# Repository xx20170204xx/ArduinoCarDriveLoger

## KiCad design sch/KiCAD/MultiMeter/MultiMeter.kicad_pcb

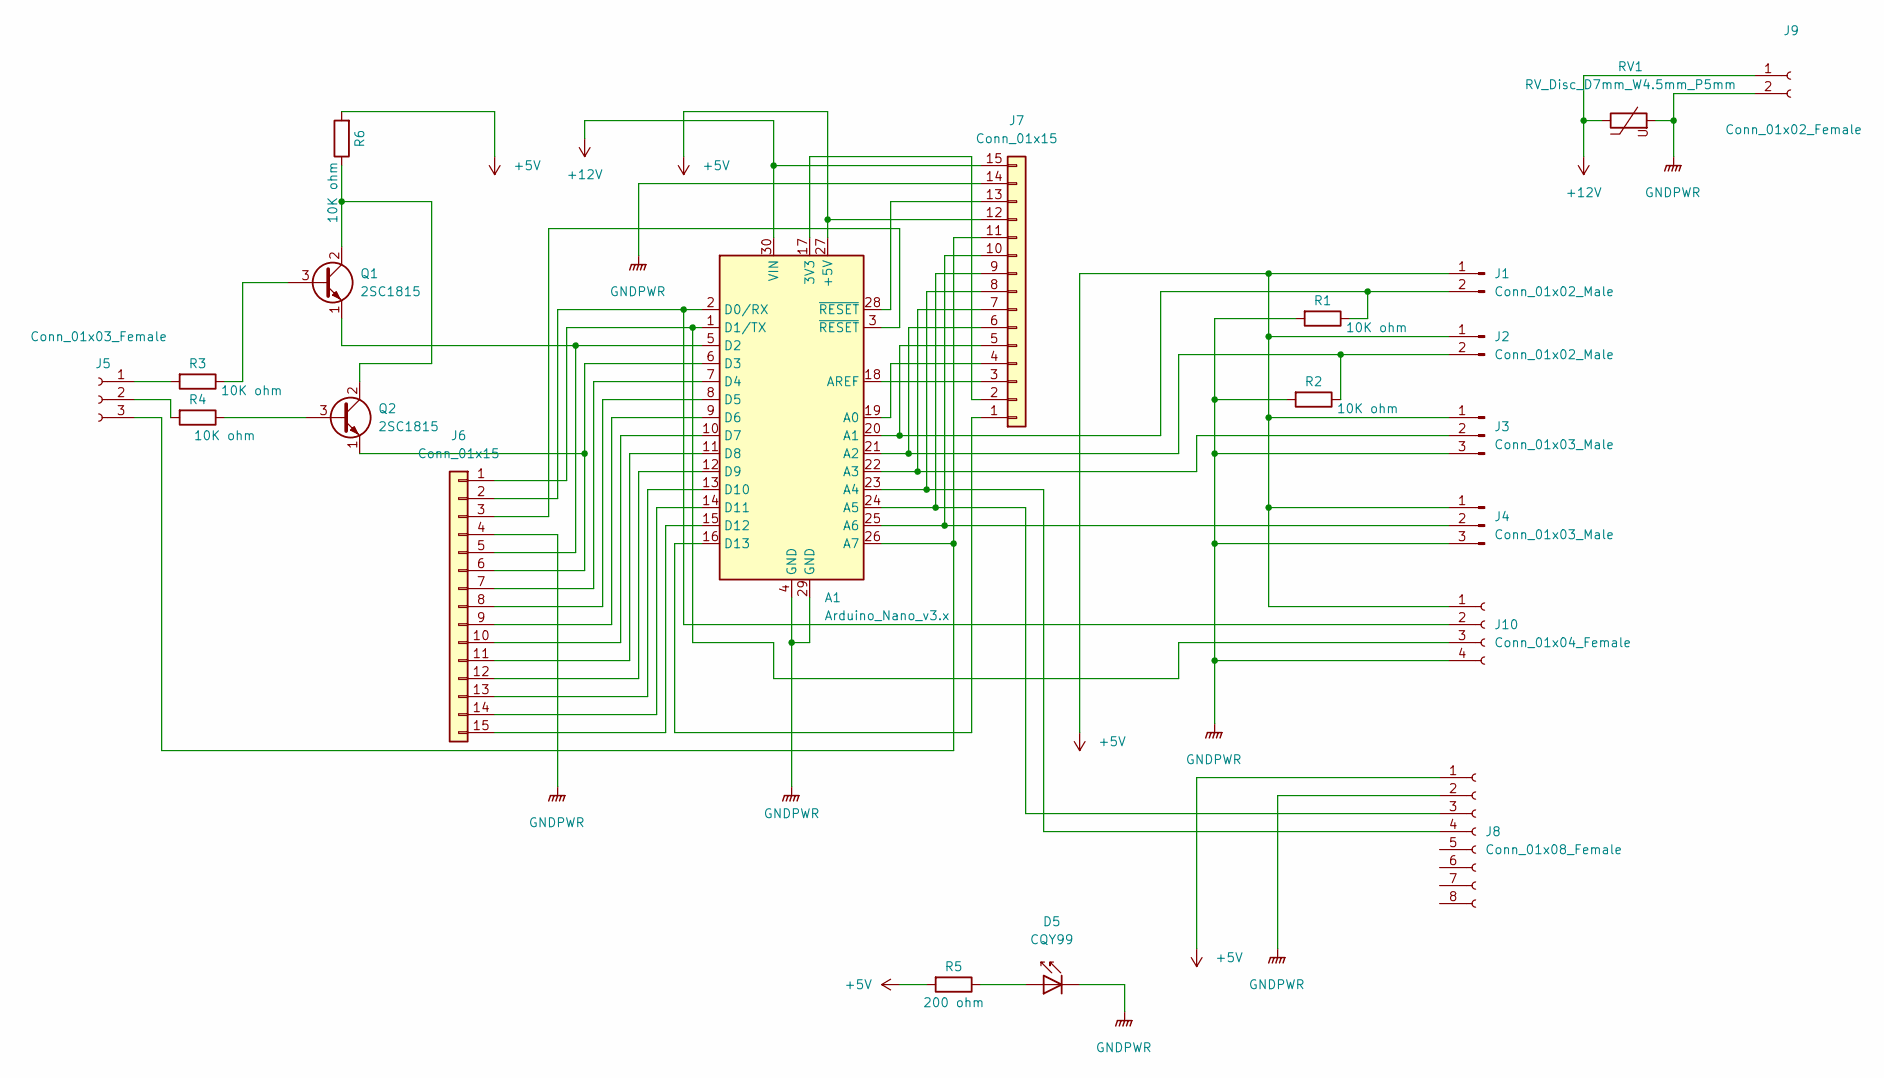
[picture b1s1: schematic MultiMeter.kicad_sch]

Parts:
A1: Arduino_Nano_v3.x; Arduino_Nano
D5: CQY99; LED_D5.0mm_IRGrey
J1, J2: Conn_01x02_Male; Molex_SPOX_5268-02A_1x02_P2.50mm_Horizontal
J3, J4: Conn_01x03_Male; Molex_SPOX_5268-03A_1x03_P2.50mm_Horizontal
J5: Conn_01x03_Female; Molex_KK-254_AE-6410-03A_1x03_P2.54mm_Vertical
J6, J7: Conn_01x15; PinSocket_1x15_P2.54mm_Vertical
J8: Conn_01x08_Female; JST_XH_S8B-XH-A-1_1x08_P2.50mm_Horizontal
J9: Conn_01x02_Female; Molex_KK-254_AE-6410-02A_1x02_P2.54mm_Vertical
J10: Conn_01x04_Female; Molex_SPOX_5268-04A_1x04_P2.50mm_Horizontal
Q1, Q2: 2SC1815; TO-92_Inline
R1, R2, R3, R4, R6: 10K ohm; R_Axial_DIN0204_L3.6mm_D1.6mm_P7.62mm_Horizontal
R5: 200 ohm; R_Axial_DIN0204_L3.6mm_D1.6mm_P7.62mm_Horizontal
RV1: RV_Disc_D7mm_W4.5mm_P5mm

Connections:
+5V: A1.27 (+5V), J1.1, J2.1, J3.1, J4.1, J7.12, J8.1, J10.1, R5.2, R6.2
+12V: A1.30 (VIN), J7.15, J9.1, RV1.1
GNDPWR: A1.4 (GND), A1.29 (GND), D5.1 (K), J3.3, J4.3, J6.4, J7.14, J8.2, J9.2, J10.4, R1.2, R2.2, RV1.2
unnamed: A1.17 (3V3), J7.2
unnamed: A1.19 (A0), J7.4
unnamed: A1.20 (A1), J1.2, J7.5, R1.1
unnamed: A1.21 (A2), J2.2, J7.6, R2.1
unnamed: A1.22 (A3), J3.2, J7.7
unnamed: A1.23 (A4), J7.8, J8.4
unnamed: A1.24 (A5), J7.9, J8.3
unnamed: A1.25 (A6), J4.2, J7.10
unnamed: A1.26 (A7), J5.3, J7.11
unnamed: A1.18 (AREF), J7.3
unnamed: A1.2 (D0/RX), J6.2, J10.2
unnamed: A1.1 (D1/TX), J6.1, J10.3
unnamed: A1.5 (D2), J6.5, Q1.1 (E)
unnamed: A1.6 (D3), J6.6, Q2.1 (E)
unnamed: A1.7 (D4), J6.7
unnamed: A1.8 (D5), J6.8
unnamed: A1.9 (D6), J6.9
unnamed: A1.10 (D7), J6.10
unnamed: A1.11 (D8), J6.11
unnamed: A1.12 (D9), J6.12
unnamed: A1.13 (D10), J6.13
unnamed: A1.14 (D11), J6.14
unnamed: A1.15 (D12), J6.15
unnamed: A1.16 (D13), J7.1
unnamed: D5.2 (A), R5.1
unnamed: J5.1, R3.2
unnamed: J5.2, R4.2
unnamed: A1.3 (~RESET), J6.3
unnamed: A1.28 (~RESET), J7.13
unnamed: Q1.3 (B), R3.1
unnamed: Q1.2 (C), Q2.2 (C), R6.1
unnamed: Q2.3 (B), R4.1

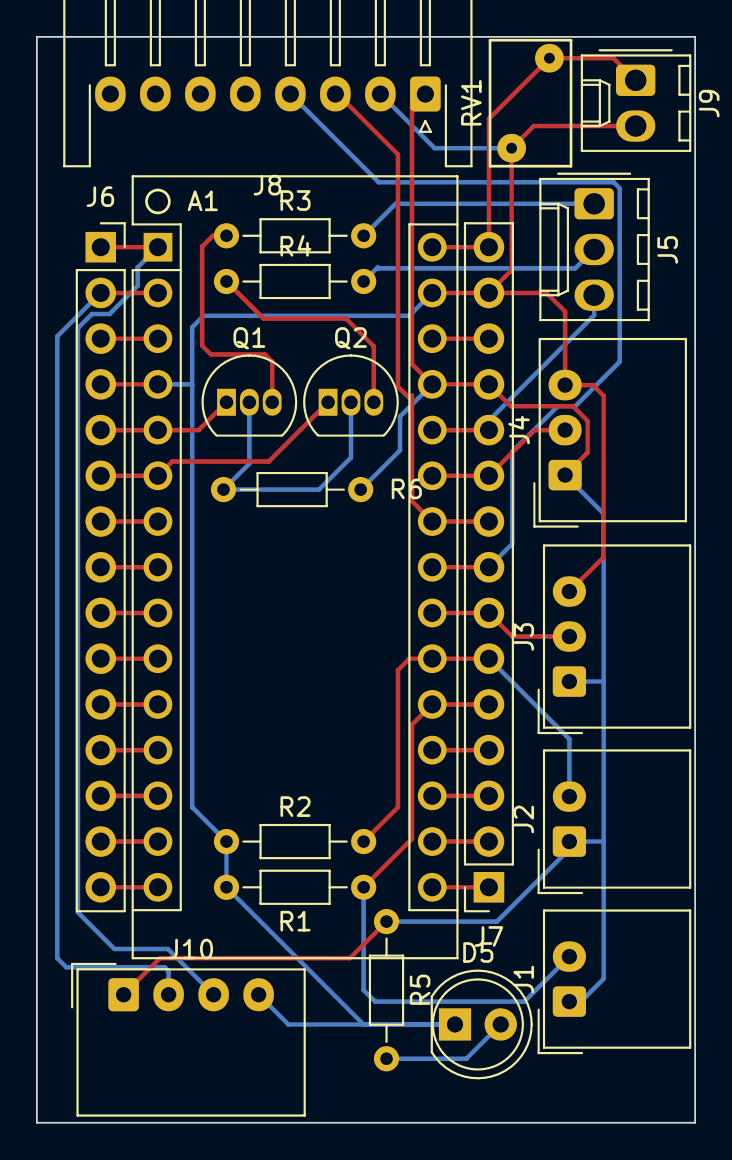
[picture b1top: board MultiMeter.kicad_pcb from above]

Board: 2 copper layers, 36.6 x 60.3 mm, 21 parts (0 on the bottom side), 35 nets.

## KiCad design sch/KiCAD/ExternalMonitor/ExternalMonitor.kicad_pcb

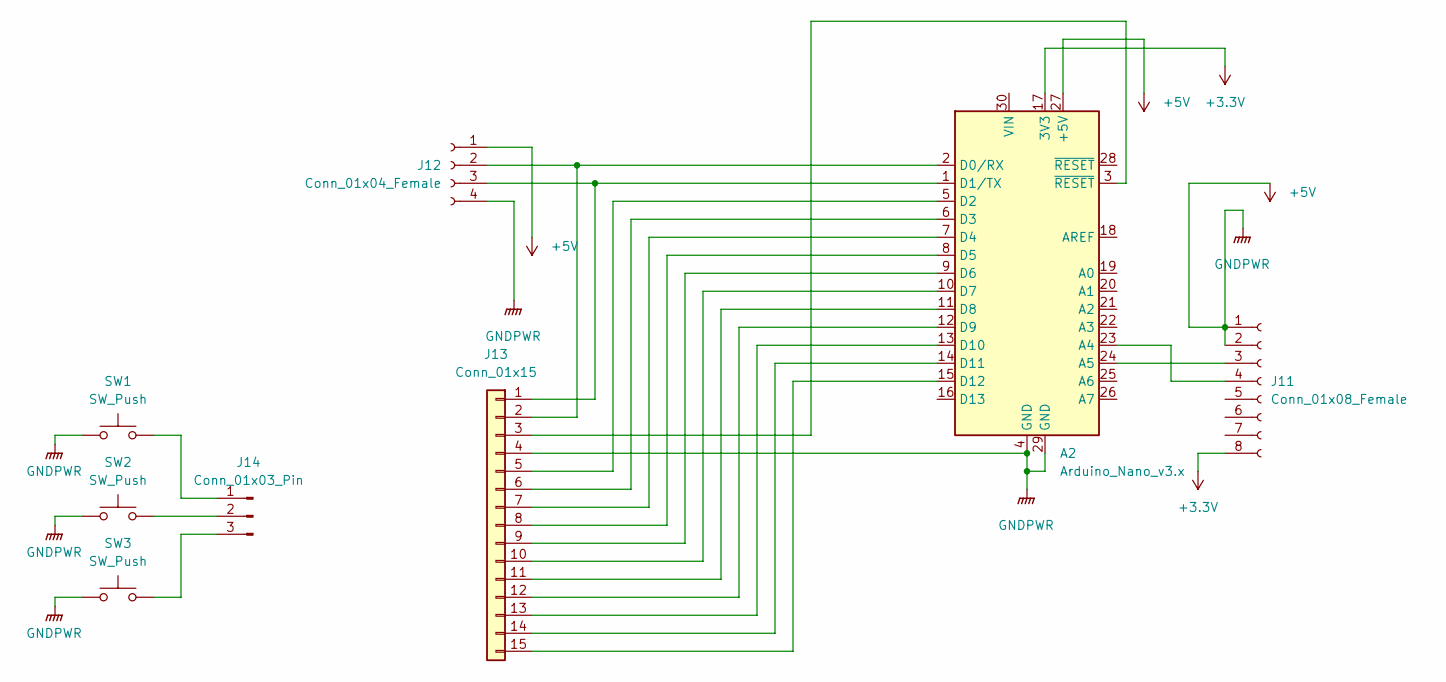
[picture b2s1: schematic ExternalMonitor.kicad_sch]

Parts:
A2: Arduino_Nano_v3.x; Arduino_Nano
J11: Conn_01x08_Female; JST_XH_S8B-XH-A-1_1x08_P2.50mm_Horizontal
J12: Conn_01x04_Female; Molex_SPOX_5268-04A_1x04_P2.50mm_Horizontal
J13: Conn_01x15; PinSocket_1x15_P2.54mm_Vertical
J14: Conn_01x03_Pin; PinHeader_1x03_P2.54mm_Vertical
SW1, SW2, SW3: SW_Push; SW_PUSH_6mm

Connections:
+3.3V: A2.17 (3V3), J11.8
+5V: A2.4 (GND), A2.27 (+5V), A2.29 (GND), J11.1, J11.2, J12.1, J12.4, J13.4, SW1.1, SW2.1, SW3.1
unnamed: A2.23 (A4), J11.4
unnamed: A2.24 (A5), J11.3
unnamed: A2.2 (D0/RX), J12.2, J13.2
unnamed: A2.1 (D1/TX), J12.3, J13.1
unnamed: A2.5 (D2), J13.5
unnamed: A2.6 (D3), J13.6
unnamed: A2.7 (D4), J13.7
unnamed: A2.8 (D5), J13.8
unnamed: A2.9 (D6), J13.9
unnamed: A2.10 (D7), J13.10
unnamed: A2.11 (D8), J13.11
unnamed: A2.12 (D9), J13.12
unnamed: A2.13 (D10), J13.13
unnamed: A2.14 (D11), J13.14
unnamed: A2.15 (D12), J13.15
unnamed: A2.3 (~RESET), J13.3
unnamed: J14.1, SW1.2
unnamed: J14.2, SW2.2
unnamed: J14.3, SW3.2

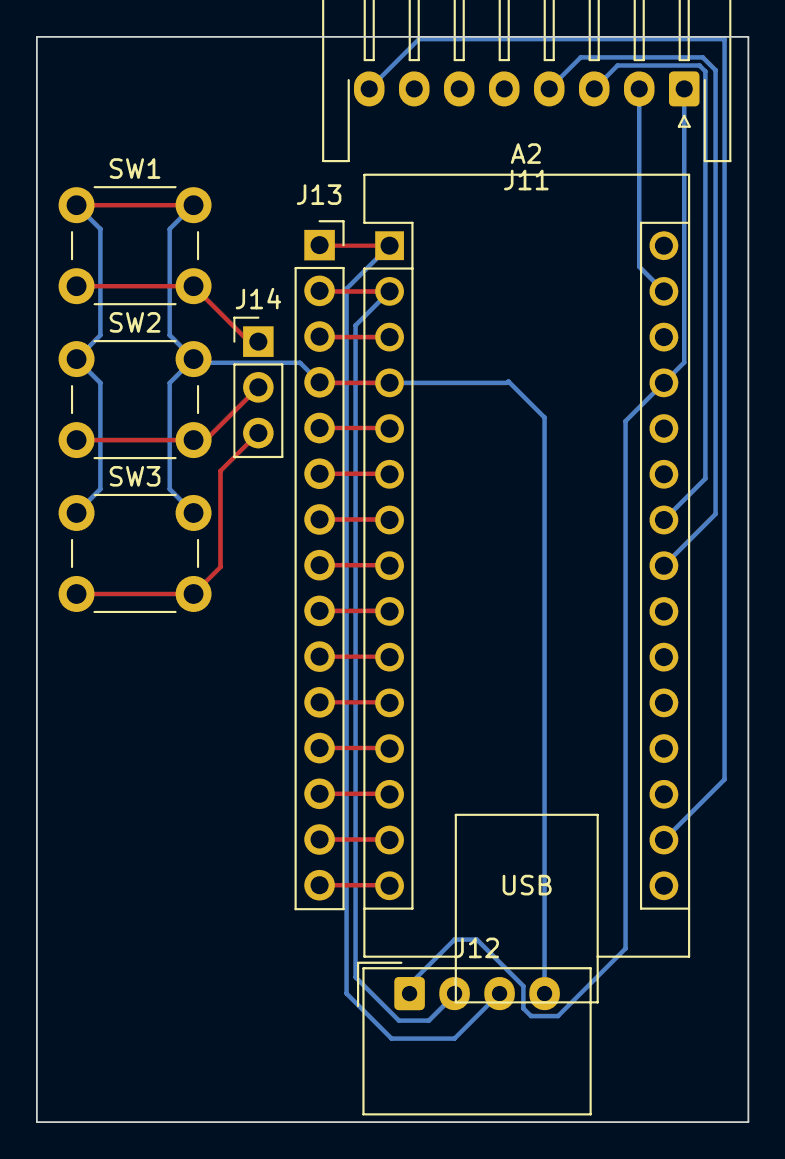
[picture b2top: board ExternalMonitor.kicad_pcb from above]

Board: 2 copper layers, 39.5 x 60.3 mm, 8 parts (0 on the bottom side), 21 nets.

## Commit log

2022-05-19 Defiのセンサーから情報を取得するプログラムを追加
2022-05-19 [未テスト]回転数/スピード取得機能追加
2022-06-12 ・LCDの表示を修正 ・一定時間車速パルスが入らない場合、速度を0Km/hに設定する ・シリアル出力に回転数/速度を追加
2022-06-15 ・デバック用にダミーの回転数、速度を出力できるようにした。 ・回転数をリセットする機能を追加
2022-06-19 警告用のピンを追加
2022-06-19 シリアル通信にて外部からのコマンドを受け付けるように修正
2022-07-13 クライアント用のプログラムを追加(Unity)
2022-07-13 SerialPortUtilityProを使用するように修正
2022-07-13 Opningの構成を修正
2022-07-13 関数の構成を修正
2022-07-13 gitclone追加
2022-07-13 単位の間違いを修正 Kpa -> bar
2022-07-13 シーンの切り替えの指定方法を修正 名前 -> インデックス 不要なメンバ関数を削除
2022-07-15 デバイスリスト表示用パネルを追加
2022-07-15 ブースト圧用関数を追加
2022-07-15 センサーの値を取得する際、指定した回数取得した平均値をを取得するように修正
2022-07-15 prefabから不要なスクリプトを削除
2022-07-15 シリアル通信で使用するデータ項目を修正（平均値を削除）
2022-07-16 接続するデバイスの情報を保存するように修正
2022-07-16 バグ修正
2022-07-16 CSV出力できるように修正
2022-07-17 ・水温/油温/油圧の値をデバック用の値を出力できるように修正
2022-07-23 ・LampMeterを追加 ・GPS位置情報を取得できるように修正 ・サブメーター設定を追加(同じ値を別の表現で表示できる)
2022-07-24 アイコンの追加
2022-07-24 TEST
2022-07-24 TEST2
2022-08-01 ・opningの背景修正 ・TachoShiftLampMeterの点灯条件を修正 ・減速比表示を正式に追加 ・(バグ要修正)画面サイズによってDeviceListが選択できない
2022-08-02 Skip機能を追加
2022-08-02 ・デバック出力を追加 ・接続出来るデバイスがUSBのみだったのを修正 ・シリアルの速度を修正(115200bps)
2022-08-02 Bluetooth用のinoを追加
2022-08-02 Bluetooth用を作成する際にバグになった部分をコメントアウト
2022-08-02 README.mdにFigureを追加
2022-08-02 画像のサイズを変更
2022-08-02 README.mdを修正
2022-08-06 ・DeviceListの表示バグを修正 ・デバイス情報の表示を簡略化
2022-08-06 companyNameを修正
2022-08-06 ・RecordButtonの表示を修正
2022-08-06 関数名変更Dev -> DevInfo
2022-08-07 MODに対応中
2022-08-07 メモ追加
2022-08-07 文字コード修正 メーターの動作修正
2022-08-14 ストップウォッチの機能を追加
2022-08-17 メーターの表示を調整
2022-08-17 Google Mapを表示できるように修正中
2022-08-17 説明などを修正
2022-08-17 KiCADで制作した物を追加
2022-08-17 回路図の間違いを修正
2022-09-12 回路図データ修正
2022-09-13 デバック用PADを追加
2022-09-15 確認用LEDを追加
2022-09-24 メーターの各種設定を変えられるように修正中
2022-09-24 Inspectorから実行できるデモモードを追加
2022-09-24 normalColorを廃止
2022-09-24 回路図微修正
2022-09-25 Voiceを出力するように修正中
2022-09-28 ・記録状態の切り替え時にSEを出力 ・ボイスを入れ替え
2022-09-28 SEを修正
2022-09-29 サウンドチェック用ツールを追加
2022-10-06 ・Mixer追加 ・音声追加 ・メーターの表示修正
2022-10-09 SEの再生条件を修正
2022-10-09 インデントを修正
2022-10-09 パネルの順番を修正
2022-10-09 初期表示でメーターの設定を取得するように修正
2022-10-10 条件修正
2022-10-10 文字コード修正
2022-10-10 SEを鳴らすように修正
2022-10-10 回転数リセットのタイミングを修正
2022-10-10 アイコンを追加
2022-10-12 回転数、速度が明らかに異常な値になるのを修正中
2022-10-12 関数の定義位置を修正
2022-10-13 ブースト圧を取得できるように修正中
2022-10-13 ブースト圧を表示できるように修正中
2022-10-13 Boostの算出方法を修正
2022-10-13 Boost周りの表示および値の範囲を修正
2022-10-13 Boostの資料を追加
2022-10-14 受信データの取り扱いを修正
2022-10-27 Androidのビルド設定を修正
2022-10-27 PIP(ピクチャーインピクチャー)用のパッチを追加
2022-10-27 AndroidManifest.xmlを修正
2022-10-27 lastDateの取り扱いを修正
2022-10-27 警告の条件を修正
2022-10-29 パッチ場所をわかりやすく修正
2022-10-30 XML保存に失敗していたのを修正
2022-11-08 Projectの作り直し
2022-12-08 誤検知防止用処理追加
2022-12-08 ・使用していない機能を削除 ・MPU6050の情報取得部分を実装
2023-02-11 MPU6050から取得した値をシリアルに出力するように修正
2023-02-12 angleをgyroに修正
2023-02-12 出力を修正
2023-03-05 未テスト
2023-03-05 Serial通信で取得したデータを取得できるように修正
2023-03-06 試行錯誤中
2023-03-20 コミット
2023-06-02 いろいろ修正
2023-06-11 データの受信方法を修正中
2023-06-11 不要なコードの削除
2023-11-04 基板修正
2023-11-04 起動時にボイス追加(案) メーターのスピードを1割増し表示(UIなし)
2023-11-04 UI修正
2023-11-04 スポーツモード追加 音声追加
2023-11-04 回路図修正
2023-11-16 外部モニター用のArduinoを作成中
2023-11-16 外部モニターを作成中
2023-11-17 回路図更新
2023-11-18 ガーバーデータ作成
2024-01-27 初期設定：Boost計
2024-01-27 間違いを修正
2024-02-03 スロットル開度表示を追加
2024-02-03 EEPROMに対応中
2024-02-03 ボタンの動作を修正
2024-02-03 ボタンの割り当てピンを修正 キャブリエーション機能を追加
2024-02-09 スロットルの表示を修正
2024-03-02 VSCode用のファイルを追加
2024-03-02 無視リスト追加
2024-03-02 ディレクトリを保持するためのファイルを追加
2024-03-02 不要な処理を削除
2024-03-02 EEPROM書き込み処理を修正
2024-03-09 回路図、パターンを修正
2024-03-12 デバッグ用コマンドを追加
2024-03-12 誤字修正
2024-03-12 回路図修正中
2024-03-15 EEPROMの情報を修正中 ３連メーターを作成中
2024-03-15 ３連メーターにスロットル情報が出るように修正
2024-03-16 回路図、基板を修正
2024-03-16 ガーバー修正
2024-03-17 回路図を複製
2024-03-17 複製した回路図の重複部分を削除
